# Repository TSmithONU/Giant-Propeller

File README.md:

# Giant Propeller

Soliwords part files, Eagle files, and Arduino files

The goal of this project was
to replace the Giant
Propeller controls with a
newer and more robust
version. The old system
used a potentiometer to
control an industrial motor
controller. The problem
with the original system is
that the potentiometer was
susceptible to being over
turned and breaking. To
remedy this, an optical split
sensor is used to measure
the speed of the hand
crank. After the speed of
the crank is read, the
onboard Teensy outputs an
analog signal to an op-amp.
That op-amp signal then
controls 0-10v to adjust the
speed of the motor
controller. All this is
assembled on a custom
circuit board. This new set
up has no physical end
points which holds up
better to children. Since
install, we have calibrated
the sensitivity, but no
repairs for everyday use.

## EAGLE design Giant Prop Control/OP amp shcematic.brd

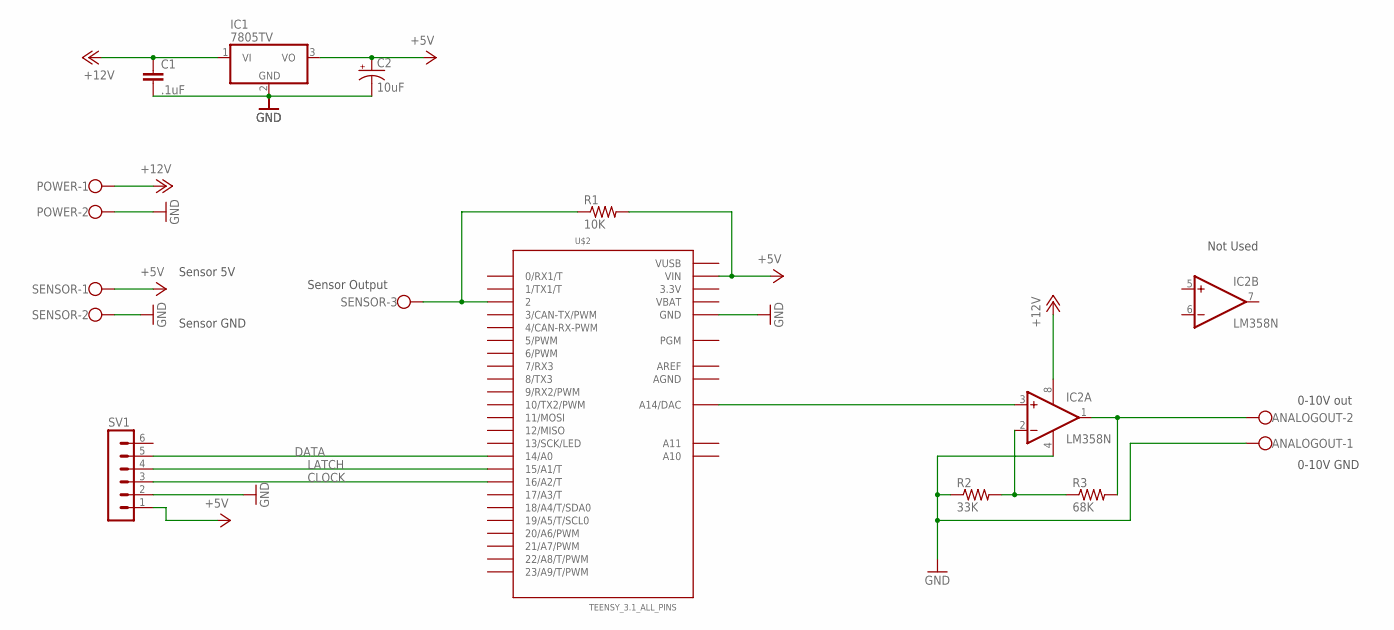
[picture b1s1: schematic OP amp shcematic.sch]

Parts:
ANALOGOUT: W237-102
C1: .1uF; C2.5-3
C2: 10uF; E2-4
IC1: 7805TV; TO220V
IC2: LM358N; DIL08
POWER: W237-102
R1: 10K; 0309/12
R2: 33K; 0309/12
R3: 68K; 0309/12
SENSOR: W237-103
SV1: MA06-1
U$2: TEENSY_3.1_ALL_PINS; TEENSY3-ALL_PINS

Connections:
3.3V: U$2.3.3V, U$2.3.3V1 (3.3V)
+5V: C2.+, IC1.3 (VO), R1.2, SENSOR.1, SV1.1, U$2.VIN
+12V: C1.1, IC1.1 (VI), IC2.8 (V+), POWER.1
AGND: U$2.AGND
AREF: U$2.AREF
CLOCK: SV1.3, U$2.16/A2 (16/A2/T)
DATA: SV1.5, U$2.14/A0
GND: ANALOGOUT.1, C1.2, C2.-, IC1.2 (GND), IC2.4 (V-), POWER.2, R2.1, SENSOR.2, SV1.2, U$2.GND, U$2.GND1 (GND)
LATCH: SV1.4, U$2.15/A1 (15/A1/T)
unnamed: IC2.3 (+IN), U$2.RESET/DAC (A14/DAC)
unnamed: ANALOGOUT.2, IC2.1 (OUT), R3.2
unnamed: R1.1, SENSOR.3, U$2.2
unnamed: IC2.2 (-IN), R2.2, R3.1
VBAT: U$2.VBAT
VUSB: U$2.VUSB

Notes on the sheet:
Sensor Output
Sensor 5V
Sensor GND
0-10V out
0-10V GND
Not Used

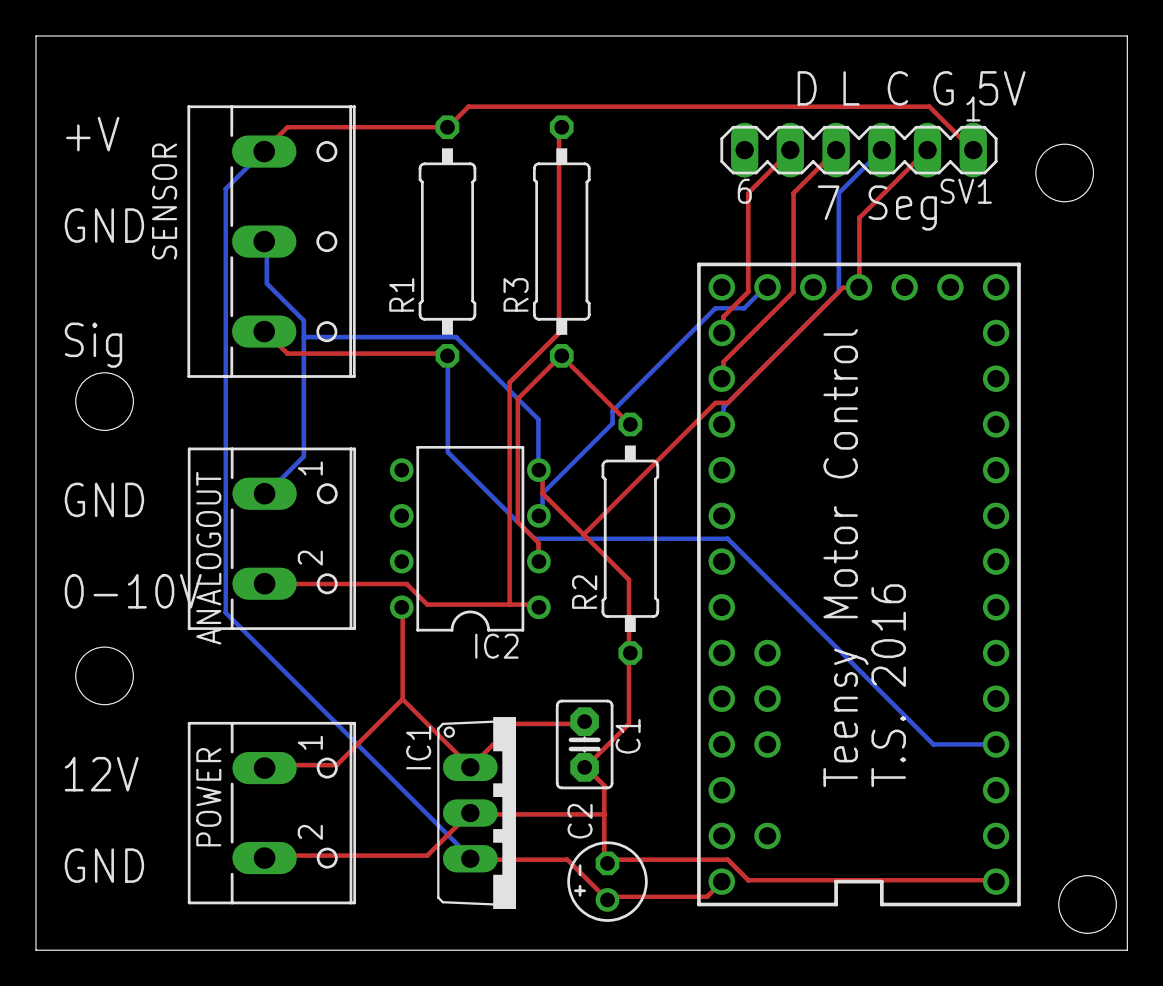
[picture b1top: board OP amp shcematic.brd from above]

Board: 2 copper layers, 60.6 x 50.8 mm, 12 parts (0 on the bottom side), 11 nets.

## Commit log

2017-07-19 Initial Upload to Git
